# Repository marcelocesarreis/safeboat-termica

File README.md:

# SAFEBOAT Térmica

Sistema de manutenção preditiva por visão térmica com IA para embarcações.
Câmera térmica própria — **MLX90640 (32×24 px) + ESP32-C3 SuperMini** — em case
estanque Ø50×62 mm impresso em ASA, com conexão Wi-Fi e alimentação 12 V do barco.

## Página do projeto

```
node server.cjs        # http://localhost:8097  (launch.json: "safeboat-termica")
```

A página (`public/index.html`) contém: visualizador 3D com vista explodida,
demo **ao vivo** da rede de análise com 3 câmeras mocadas, método de
comparação/detecção, esquema elétrico, cabeamento, fixação, fabricação e BOM.

## Rede de análise (`public/engine.js`)

Implementação de referência do pipeline, idêntica no navegador (mock) e em Node:

1. Aquisição 32×24 @ 4 Hz por I²C, dentro da câmera
2. Normalização (Ta do sensor)
3. Baseline por pixel (média+σ, Welford) por regime de operação
4. Comparação: Δ e z-score (anomalia: z>4 **e** Δ>6 °C)
5. Blobs (componentes conectados ≥3 px)
6. Persistência temporal (≥3 frames)
7. Classificação por zona de equipamento + severidade
8. Alerta com diagnóstico sugerido

Com hardware real: `public/bancada.html` (USB) já alimenta o detector com quadros do sensor.
Rede: ver `firmware/PLANO-WIFI.md` — HTTPS para o hub, receita do VIB, sem MQTT.

## Hardware

- Módulo MLX90640 (GY-MCU90640) via I²C (GPIO8/9, 400 kHz) no ESP32-C3
- Buck MP1584EN 12→5 V + TVS SMBJ26A; MLX no 3V3 do ESP
- Janela frontal de **germânio Ø25×1** (vidro comum bloqueia 8–14 µm);
  alternativa de bancada: filme HDPE 0,25 mm no mesmo recesso
- Vedação (rev. C): tampa de **baioneta 60°** + O-ring NBR 37×3 radial + prensa-cabo M12 IP68
  (a rosca impressa da rev. B falhou: 0,50 mm de engajamento contra 0,20–0,45 mm de erro de FDM)

## CAD paramétrico

```
node tools/generate-stl.cjs    # regenera stl/*.stl (corpo, tampa, carrier, suporte)
```

Mesma receita validada no projeto Vigia (`../safeboat-camera-nv`).

## Retomar o projeto em outra máquina

Este ramo (`projeto`) tem o código-fonte completo; o ramo `main` é só o site publicado no GitHub Pages
(cópia de `public/` + `stl/` + `firmware/`).

```
git clone -b projeto https://github.com/marcelocesarreis/safeboat-termica.git
cd safeboat-termica
npm install            # JSCAD, three, pngjs (CAD e página)
npm start              # servidor local + hub de teste em http://localhost:8097  (Bancada: /bancada.html)
npm run stl            # regenera os STL da rev. C;  node tools/verify-fit.cjs confere a montagem
node tools/test-parser.cjs
```

Firmware (placa ESP32-C3 SuperMini + MLX90640, fonte em `firmware/termica/termica.ino`, versão atual 0.2.8):

```
arduino-cli core install esp32:esp32@3.3.10
arduino-cli lib install "Adafruit MLX90640"
arduino-cli compile --fqbn esp32:esp32:esp32c3:CDCOnBoot=cdc,PartitionScheme=min_spiffs --build-path firmware/build-termica firmware/termica
arduino-cli upload -p COMx --fqbn esp32:esp32:esp32c3:CDCOnBoot=cdc,PartitionScheme=min_spiffs --input-dir firmware/build-termica
```

Use sempre a MESMA `--build-path` (a primeira compilação é longa; as seguintes são rápidas). Os binários prontos da
0.2.8 estão em `firmware/build-termica-0.2.8/` — dá para gravar sem compilar. Ferramentas Python (`pip install pyserial bleak`):
`tools/wifi-cmd.py` (comandos pela USB; recusa o comando de senha), `tools/ble-test.py` (teste do Bluetooth), `tools/serial-dump.py`.

Estado em 19/09/2026: USB, Wi-Fi (HTTPS ao hub, sem MQTT) e Bluetooth LE funcionando; o sensor MLX90640 parou de
responder no I²C (conferir os 4 fios 3V3/GND/GPIO8=SDA/GPIO9=SCL). Próxima etapa: 0.3, detector a bordo — ver `firmware/PLANO-WIFI.md`.
A senha do Wi-Fi fica só na NVS da placa (digitada na Bancada pela USB); não está em nenhum arquivo do repositório.

## Hardware — PCB v1 (22/09/2026)

Placa própria em `hardware/pcb/` (KiCad 10, gerada por script): **quadrada 32 × 32 mm** para o case cúbico do render
(~36 mm externo), **montagem completa na JLCPCB (Standard, dois lados)**: ESP32-C3-MINI-1 + buck AP63203 (12 V → 3,3 V)
+ proteção (PPTC, TVS, SS34) + borne parafuso 12 V + JST p/ rabicho USB na ré; **MLX90640 110°×75°** (TO-39, THT) na
frente. Mesma pinagem do firmware (SDA 8 / SCL 9 / LED 10) + GPIO4 (corta o sensor) e GPIO0 (tensão do barco).
Pacote JLCPCB pronto (gerbers + BOM + CPL), esquemático com ERC 0 e netlist conferida contra a placa —
ver `hardware/pcb/README.md`. A versão redonda Ø41,4 (case escotilha, sensor 55°) ficou em `hardware/pcb/kicad/legado-redonda/`;
o corpo rev. D (ombro z=14) e `stl/espacador-pcb.stl` valem só para ela. Case cúbico em JSCAD: a fazer.

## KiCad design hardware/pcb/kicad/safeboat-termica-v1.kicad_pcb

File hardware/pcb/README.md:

# SAFEBOAT TÉRMICA v2 — PCB (KiCad 10) · pacote JLCPCB (montagem completa)

Rev. 2 (reunião de equipe de 22/10/2026). Placa **40 × 40 mm, 4 camadas (F sinais · In1 plano GND · In2 plano 3V3 ·
B sinais), 1,6 mm**, cantos R2, **recortes laterais na antena**. **Montagem completa na JLCPCB (Standard PCBA, dois
lados)**: SMD + JST no lado da ré (F) e o **sensor MLX90640 110°×75° (TO-39, THT) no lado da frente (B)**. Chega
pronta: só soldar os 2 fios de alimentação nos pads e gravar o firmware.

Versões anteriores: redonda Ø41,4 (case escotilha, sensor 55°) em `kicad/legado-redonda/`; quadrada 32 × 32 de 2 camadas
(v1, 22/09) só no histórico do git.

## O que mudou na rev. 2 (pedidos da reunião)

| Pedido | O que foi feito |
|---|---|
| Nada metálico perto da antena | Indutor, botões, JST e diodos saíram do topo; acima de y = +14,35 só existe o módulo. Faixas laterais do módulo só com 0603/0805 e o SOT-23 do PMOS. |
| Diretrizes de layout da Espressif | Antena rente à borda **com recortes de 3,3 mm nos dois lados** ("cut out the base board on both sides of the antenna"), keep-out de cobre nas 4 camadas sob a antena e recortes, plano de GND sólido sob o módulo (In1), vias de GND, 10 µF + 100 nF no 3V3 junto ao pino, RC no EN, USB longe da antena (canto inferior esquerdo). |
| Trilhas a 90° nos pads | Roteador travado em **ninety_degree**: todas as trilhas são ortogonais, entram reto em todos os pads. |
| Menos voltas / mais planos | **4 camadas**: In1 = GND sólido, In2 = 3V3 sólido; o roteador não roteia nos planos (só fura para eles), então sobram poucas trilhas em F/B. |
| Clearance × limites JLC | Isolamento **0,2 mm** (JLC 4 camadas: ≥ 0,127), trilha 0,25, via 0,6/0,3 (JLC ≥ 0,45/0,2), cobre–borda 0,3, furo–furo ≥ 0,5; regras gravadas no `.kicad_pro`. |
| 4 furos de fixação longe da antena | **M2,5 (Ø2,7)** em (±17,5; +3) e (±17,5; −18): padrão 35 × 21 mm; os de cima ficam 11 mm abaixo do início da antena e 7,6 mm fora do recorte. Raio livre de 2,3 mm para a cabeça. |
| Fusível na entrada | Mantido: **F1 PPTC 0,5 A / 60 V** (SMD1812P050TF/60) + fusível 1 A em linha no cabo. |
| Alimentação 8–32 V | O AP63203 (32 V abs. max.) e o TVS de 26 V **saíram**. Entrou **MP4560** (3,8–55 V, 2 A, abs. max. 60 V), **TVS SMBJ33A** (standoff 33 V, clamp 53 V) e capacitores de entrada **4,7 µF/100 V**. Divisor de leitura da tensão virou 330k/15k (55 V → 2,4 V no ADC). |
| Sem conector de alimentação | Borne removido; **pads P1 (+VIN, quadrado) e P2 (GND)** Ø2,6 / furo 1,3 para soldar o fio direto. |

## O que está aqui

| Pasta / arquivo | Conteúdo |
|---|---|
| `kicad/safeboat-termica-v1.kicad_pcb` + `.kicad_pro` | placa roteada (abre no KiCad 10) — DRC: ver `kicad/drc.json` |
| `kicad/safeboat-termica-v1.kicad_sch` · `safeboat-termica-v1-esquematico.pdf` | **esquemático** (ERC; netlist conferida contra a PCB por `compare_netlist.py`) |
| `kicad/render-*.png` · `layout-*.svg` · `revisao/` | renders 3D (com modelos do sensor e dos pads), vistas 2D, pacote para revisão |
| `jlcpcb/safeboat-termica-v1-gerbers.zip` | gerbers 4 camadas + furação (RS-274X / Excellon) — upload no pedido |
| `jlcpcb/BOM-safeboat-termica-v1.csv` · `CPL-safeboat-termica-v1.csv` | BOM (todas as linhas com código LCSC) e posições (U3 = Bottom) |
| `make_board.py` | fase 1: contorno com recortes, furos, footprints próprios (sensor), **netlist pino a pino**, keep-out, planos, DSN a 90° |
| `finish_board.py` · `fix_drc.py` | fase 2: importa o SES do Freerouting, alarga potência, costura de GND, serigrafia + logo, `.kicad_pro`; pós-DRC |
| `gen_schematic.py` · `compare_netlist.py` | esquemático a partir da mesma netlist · conferência esquemático × PCB |
| `check_overlaps.py` · `export_jlcpcb.py` · `make_gerbers.sh` · `pipeline_final.sh` | courtyards reais, recortes, furos · BOM/CPL · gerbers · pipeline completo |
| `lib/` · `make_3d_models.cjs` · `add_models.py` | símbolo/footprint Espressif; modelos 3D próprios (VRML) do sensor |

## Circuito (resumo — netlist completa em `make_board.py`)

- **Entrada 8–32 V**: P1/P2 (fio soldado; fusível 1 A no cabo) → F1 PPTC 0,5 A/60 V → D1 TVS SMBJ33A → D2 SS34 em série
  (inversão de polaridade) → VIN.
- **Buck U2 MP4560** (não síncrono, 2 A): **FREQ R11 200k → 488 kHz**; FB 0,8 V com **R9 47k / R10 15k → 3,31 V**
  (valores básicos da JLC); COMP **R12 68k + C12 1 nF**; BST C8 100 nF; entrada C5 + C11 4,7 µF/100 V; **L1 10 µH
  SWPA5040S** (2,1 A); roda livre **D4 SS36** (60 V); saída C6/C7 2×22 µF. **EN fica flutuante (= ligado)**: o pino tem
  máximo absoluto de 5 V e não pode ir ao VIN.
- **USB de bancada**: J1 JST-PH 4 vias (1 5V · 2 D− · 3 D+ · 4 GND) → D3 SS14 → VIN. Liga só no USB; com o barco ligado o D3 bloqueia.
- **MCU U1 ESP32-C3-MINI-1-N4**: GPIO8 SDA · GPIO9 SCL (+ BOOT SW1) · GPIO10 LED · GPIO4 SENS_OFF · GPIO0 VSENSE
  (R7 330k / R8 15k + C4) · GPIO18/19 USB · EN com R1 10k + C1 1 µF + SW2 RST · C9 10 µF + C10 100 nF.
- **Sensor U3 MLX90640ESF-BAA** (110°; 1 SDA · 2 VDD · 3 GND · 4 SCL) em VDD_MLX = 3V3 via Q1 SI2301 (ligado por
  padrão; GPIO4 alto desliga); C2 100 nF + C3 10 µF; pull-ups R2/R3 2k2 para VDD_MLX.

## Mecânica

- Lente do sensor em (0; −12) da placa (descentrada: o módulo de 16,6 mm ocupa o topo). Lata Ø9,3 × 5,7 mm na frente;
  decisão de 13/10: **lata exposta** pelo furo do case com anel de vedação em volta, sem janela de germânio.
- Ré: JST 6 mm + plugue, indutor 4 mm, botões 2 mm. Case externo ≈ 44 × 44 × 28 mm com paredes de 2 mm.
- Furos M2,5 em (±17,5; +3) e (±17,5; −18) — postes de Ø5 no case, cabeça ≤ Ø4,6.

## Pedido na JLCPCB

1. **PCB**: upload de `jlcpcb/safeboat-termica-v1-gerbers.zip` — **4 camadas**, 1,6 mm, stack-up padrão JLC04161H, HASL ou
   ENIG, 5 unidades.
2. **PCBA Standard, "Both sides"**: upload de `BOM-safeboat-termica-v1.csv` + `CPL-safeboat-termica-v1.csv`. U3 aparece
   com Layer = Bottom; confirmar no viewer que o sensor está do lado oposto ao módulo.
3. **Códigos LCSC** (todas as linhas): U1 C2934569 · U2 **C40133** (MP4560, US$ 4,45) · U3 **C17380659** (MLX90640 110°,
   ~US$ 28, estoque LCSC 34 un. em 13/10) · Q1 C10487 · D1 **C173526** (SMBJ33A) · D2 C8678 · D3 C2480 · D4 **C360444**
   (SS36A) · L1 **C84608** (SWPA5040S-100) · F1 C462518 · J1 C131334 · SW1/SW2 C72443 · LED1 C157740 · C5/C11
   **C337978** (4,7 µF 100 V) · C6/C7 C45783 · C9 C15850 · C3 C19702 · C1 C15849 · 100 nF C14663 · C12 C1588 ·
   R1 C25804 · R2/R3 C4190 · R4/R6 C21190 · R5 C25803 · R7 C23137 · R8/R10 C22809 · R9 C25819 · R11 C25811 · R12 C23231.
   Os de R9/R11/R12/C12/R7/R8 vieram do guia de básicos da JLC — conferir no carrinho (editar peça desmarca a linha).
4. Depois de chegar: soldar os 2 fios nos pads (+VIN no quadrado), gravar o firmware pelo rabicho USB (BOOT + RST).

## Pendências

- Case cúbico em JSCAD (furo da lata + anel, postes M2,5, prensa-cabo na ré).
- Bancada: consumo em 8/12/24/32 V, ripple no VDD do sensor, aquecimento do MP4560, teste de surto.
- Firmware: GPIO4 e GPIO0; engine com FOV 110°.

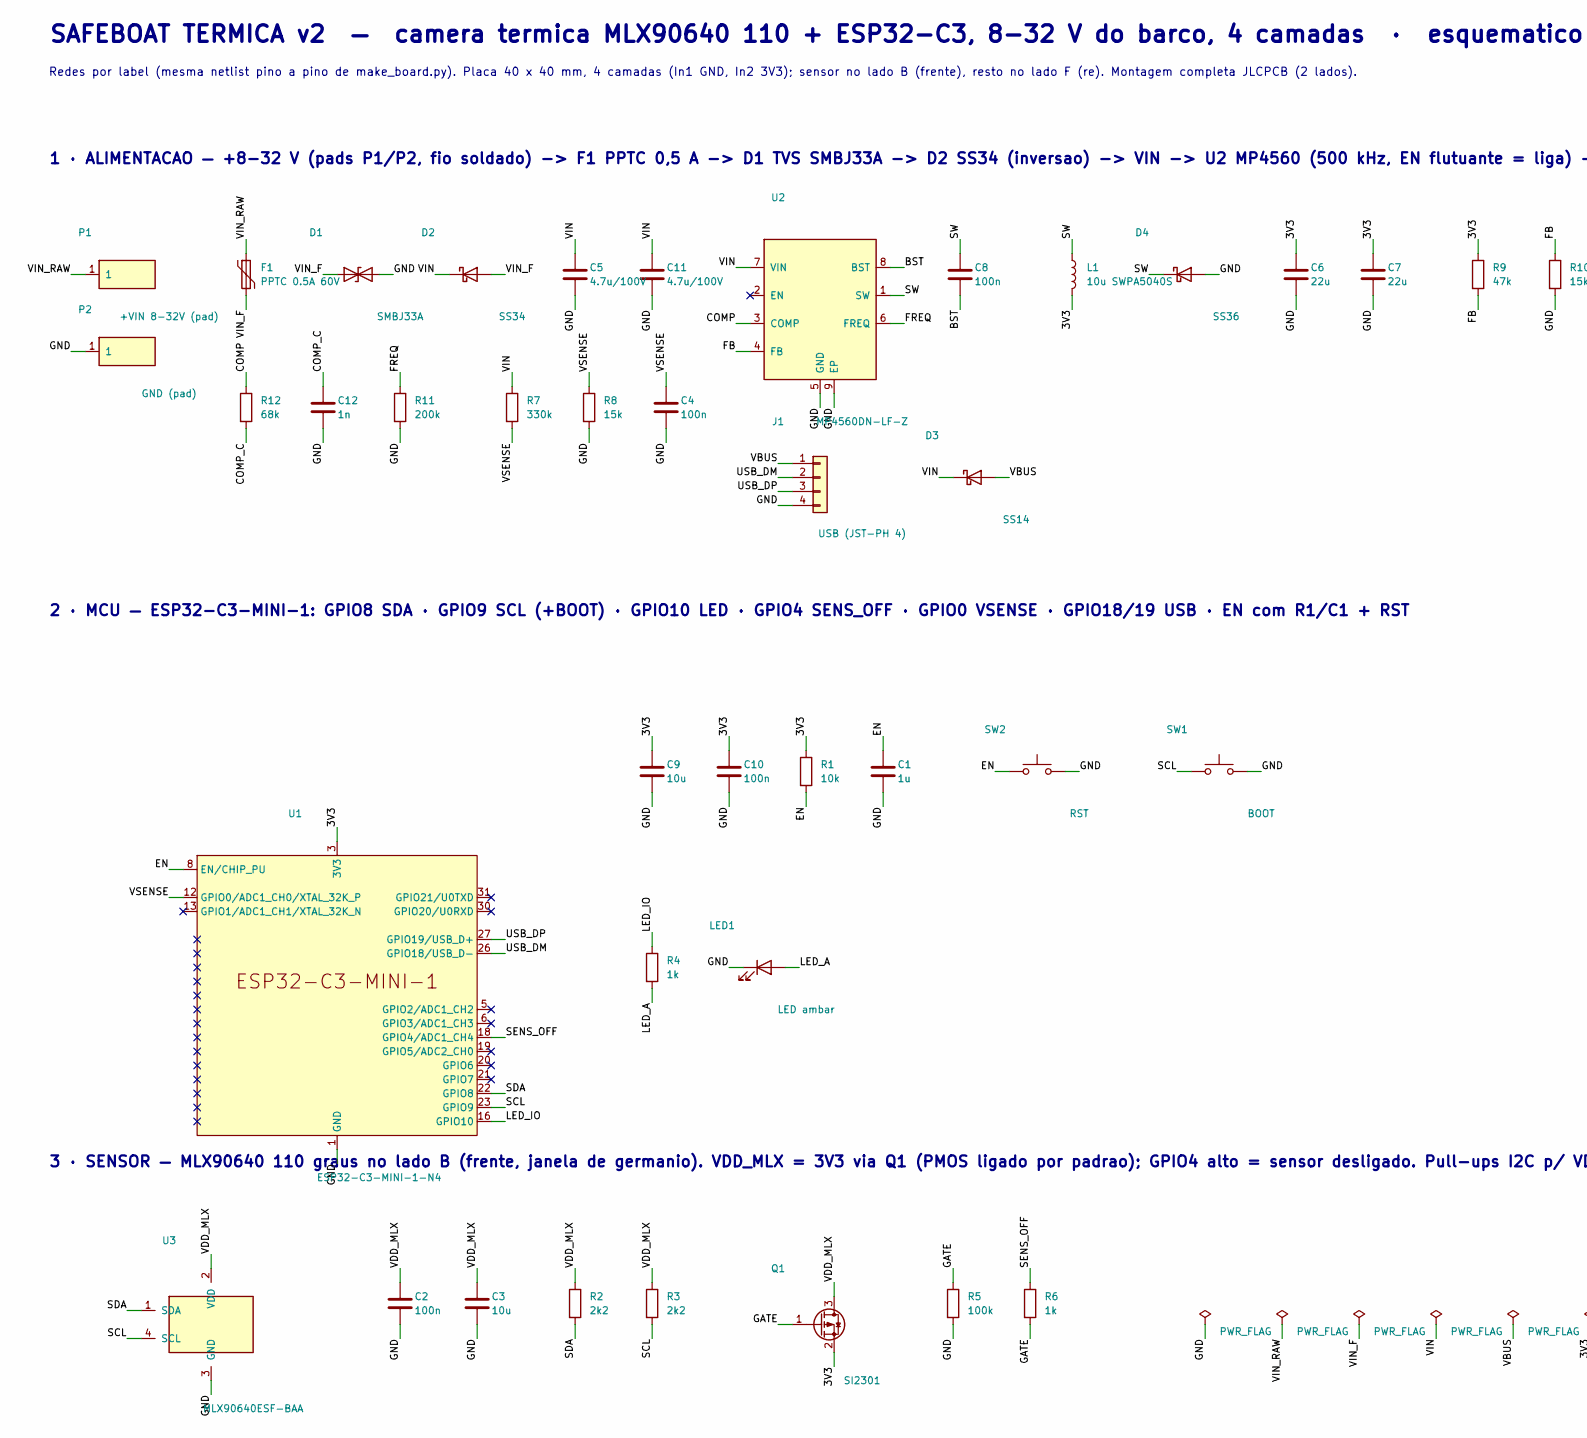
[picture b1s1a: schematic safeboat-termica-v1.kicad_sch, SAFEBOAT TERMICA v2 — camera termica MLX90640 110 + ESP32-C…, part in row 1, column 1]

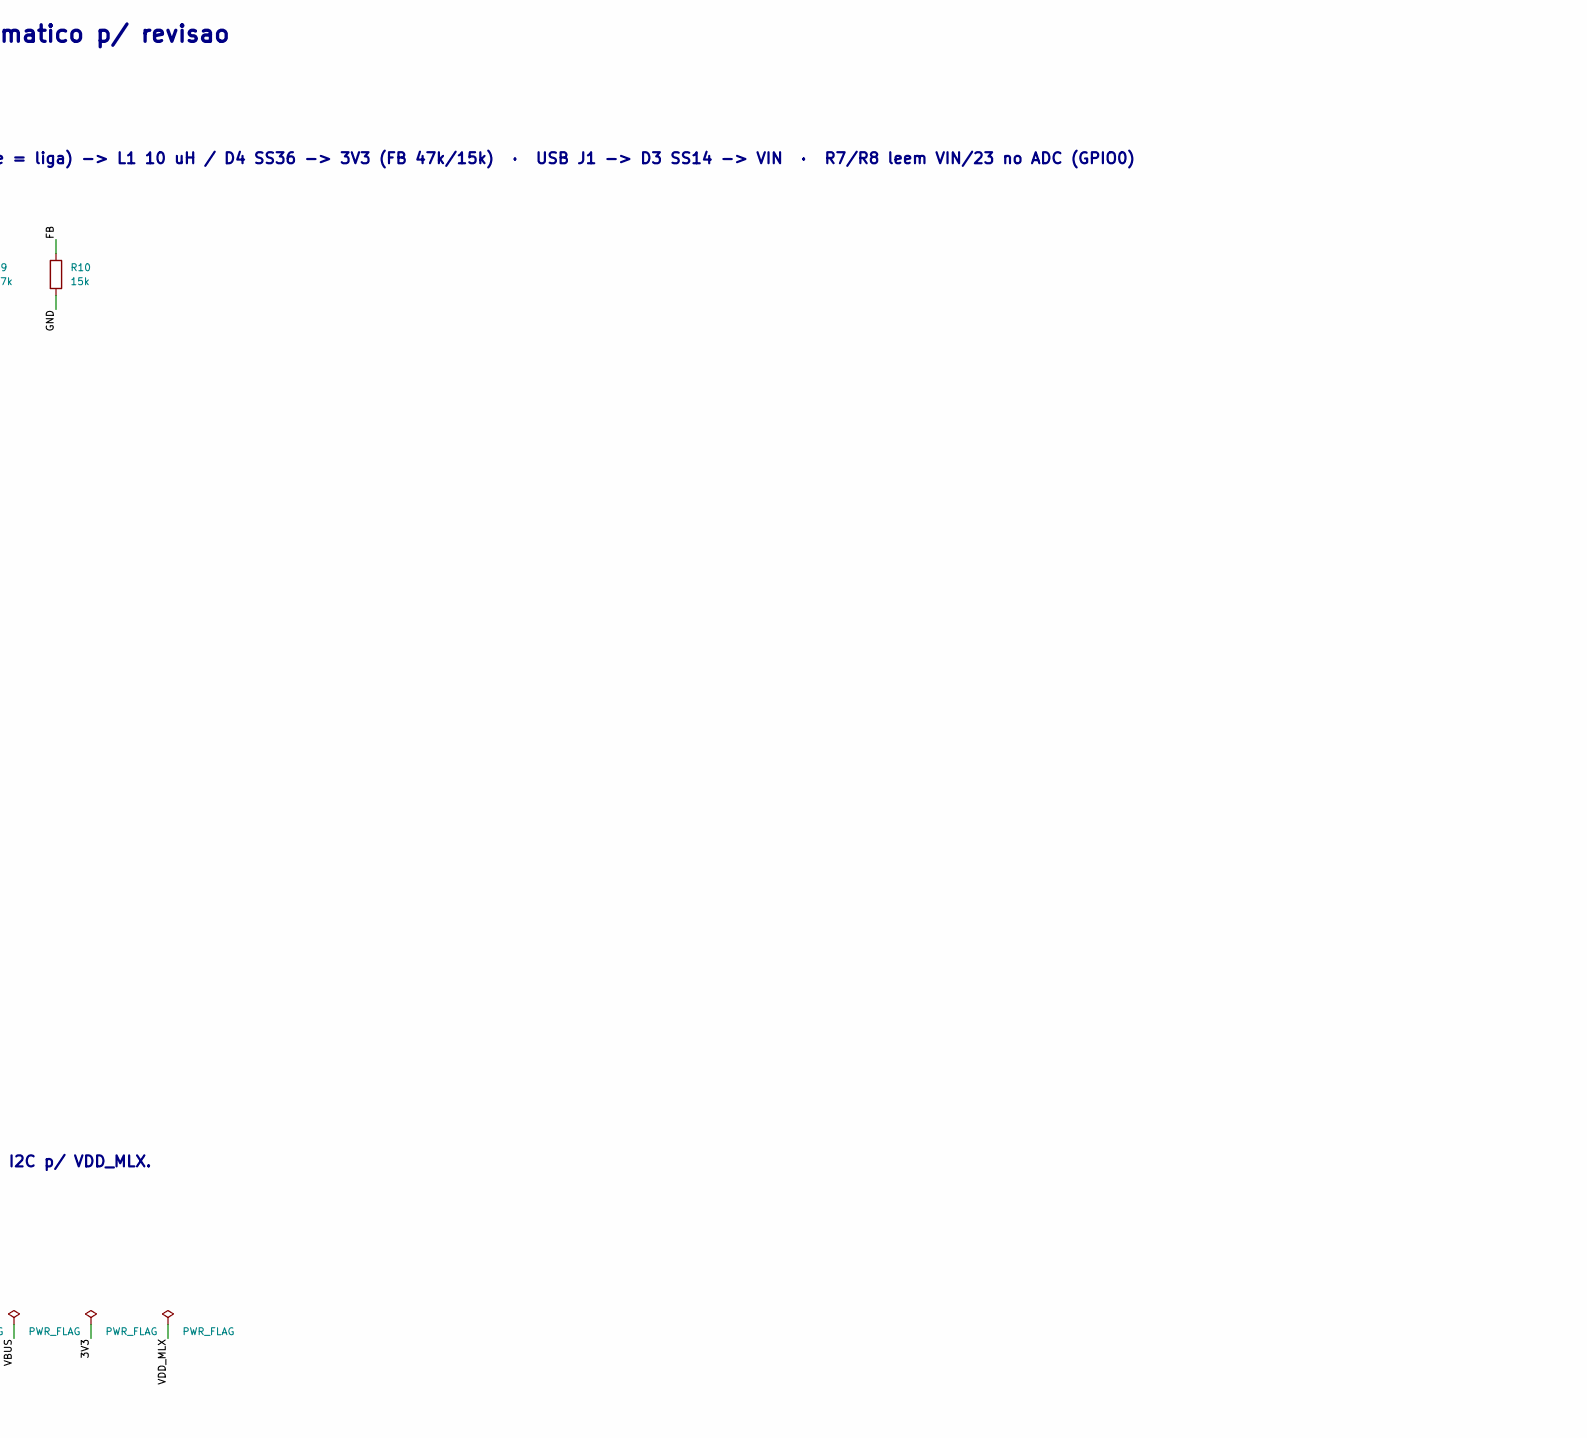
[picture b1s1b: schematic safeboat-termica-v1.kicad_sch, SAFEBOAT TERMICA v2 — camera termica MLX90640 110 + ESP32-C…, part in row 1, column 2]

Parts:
C1: 1u; C_0603_1608Metric
C2, C4, C8, C10: 100n; C_0603_1608Metric
C3: 10u; C_0603_1608Metric
C5, C11: 4.7u/100V; C_1210_3225Metric
C6, C7: 22u; C_0805_2012Metric
C9: 10u; C_0805_2012Metric
C12: 1n; C_0603_1608Metric
D1: SMBJ33A; D_SMB
D2: SS34; D_SMA
D3: SS14; D_SMA
D4: SS36; D_SMA
F1: PPTC 0.5A 60V; Fuse_1812_4532Metric
J1: USB (JST-PH 4); JST_PH_B4B-PH-K_1x04_P2.00mm_Vertical
L1: 10u SWPA5040S; L_Sunlord_SWPA5040S
LED1: LED ambar; LED_0603_1608Metric
P1: +VIN 8-32V (pad); WirePad_P1
P2: GND (pad); WirePad_P2
Q1: SI2301; SOT-23
R1: 10k; R_0603_1608Metric
R2, R3: 2k2; R_0603_1608Metric
R4, R6: 1k; R_0603_1608Metric
R5: 100k; R_0603_1608Metric
R7: 330k; R_0603_1608Metric
R8, R10: 15k; R_0603_1608Metric
R9: 47k; R_0603_1608Metric
R11: 200k; R_0603_1608Metric
R12: 68k; R_0603_1608Metric
SW1: BOOT; SW_Push_1P1T_NO_CK_KMR2
SW2: RST; SW_Push_1P1T_NO_CK_KMR2
U1: ESP32-C3-MINI-1-N4; ESP32-C3-MINI-1
U2: MP4560DN-LF-Z; HSOP-8-1EP_3.9x4.9mm_P1.27mm_EP2.41x3.1mm_ThermalVias
U3: MLX90640ESF-BAA; MLX90640_TO-39

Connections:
3V3: C6.1, C7.1, C9.1, C10.1, L1.2, Q1.2 (S), R1.1, R9.1, U1.3 (3V3)
BST: C8.2, U2.8 (BST)
COMP: R12.1, U2.3 (COMP)
COMP_C: C12.1, R12.2
EN: C1.1, R1.2, SW2.1, U1.8 (EN/CHIP_PU)
FB: R9.2, R10.1, U2.4 (FB)
FREQ: R11.1, U2.6 (FREQ)
GATE: Q1.1 (G), R5.1, R6.2
GND: C1.2, C2.2, C3.2, C4.2, C5.2, C6.2, C7.2, C9.2, C10.2, C11.2, C12.2, D1.2 (A2), D4.2 (A), J1.4, LED1.1 (K), P2.1, R5.2, R8.2, R10.2, R11.2, SW1.2, SW2.2, U1.1 (GND), U1.2 (GND), U1.11 (GND), U1.14 (GND), U1.36 (GND), U1.37 (GND), U1.38 (GND), U1.39 (GND), U1.40 (GND), U1.41 (GND), U1.42 (GND), U1.43 (GND), U1.44 (GND), U1.45 (GND), U1.46 (GND), U1.47 (GND), U1.48 (GND), U1.49 (GND), U1.50 (GND), U1.51 (GND), U1.52 (GND), U1.53 (GND), U2.5 (GND), U2.9 (EP), U3.3 (GND)
LED_A: LED1.2 (A), R4.2
LED_IO: R4.1, U1.16 (GPIO10)
SCL: R3.2, SW1.1, U1.23 (GPIO9), U3.4 (SCL)
SDA: R2.2, U1.22 (GPIO8), U3.1 (SDA)
SENS_OFF: R6.1, U1.18 (GPIO4/ADC1_CH4)
SW: C8.1, D4.1 (K), L1.1, U2.1 (SW)
USB_DM: J1.2, U1.26 (GPIO18/USB_D-)
USB_DP: J1.3, U1.27 (GPIO19/USB_D+)
VBUS: D3.2 (A), J1.1
VDD_MLX: C2.1, C3.1, Q1.3 (D), R2.1, R3.1, U3.2 (VDD)
VIN: C5.1, C11.1, D2.1 (K), D3.1 (K), R7.1, U2.7 (VIN)
VIN_F: D1.1 (A1), D2.2 (A), F1.2
VIN_RAW: F1.1, P1.1
VSENSE: C4.1, R7.2, R8.1, U1.12 (GPIO0/ADC1_CH0/XTAL_32K_P)

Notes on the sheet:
SAFEBOAT TERMICA v2 — camera termica MLX90640 110 + ESP32-C3, 8-32 V do barco, 4 camadas · esquematico p/ revisao
Redes por label (mesma netlist pino a pino de make_board.py). Placa 40 x 40 mm, 4 camadas (In1 GND, In2 3V3); sensor no lado B (frente), resto no lado F (re). Montagem completa JLCPCB (2 lados).
1 · ALIMENTACAO — +8-32 V (pads P1/P2, fio soldado) -> F1 PPTC 0,5 A -> D1 TVS SMBJ33A -> D2 SS34 (inversao) -> VIN -> U2 MP4560 (500 kHz, EN flutuante = liga) -> L1 10 uH / D4 SS36 -> 3V3 (FB 47k/15k) · USB J1 -> D3 SS14 -> VIN · R7/R8 leem VIN/23 no ADC (GPIO0)
2 · MCU — ESP32-C3-MINI-1: GPIO8 SDA · GPIO9 SCL (+BOOT) · GPIO10 LED · GPIO4 SENS_OFF · GPIO0 VSENSE · GPIO18/19 USB · EN com R1/C1 + RST
3 · SENSOR — MLX90640 110 graus no lado B (frente, janela de germanio). VDD_MLX = 3V3 via Q1 (PMOS ligado por padrao); GPIO4 alto = sensor desligado. Pull-ups I2C p/ VDD_MLX.

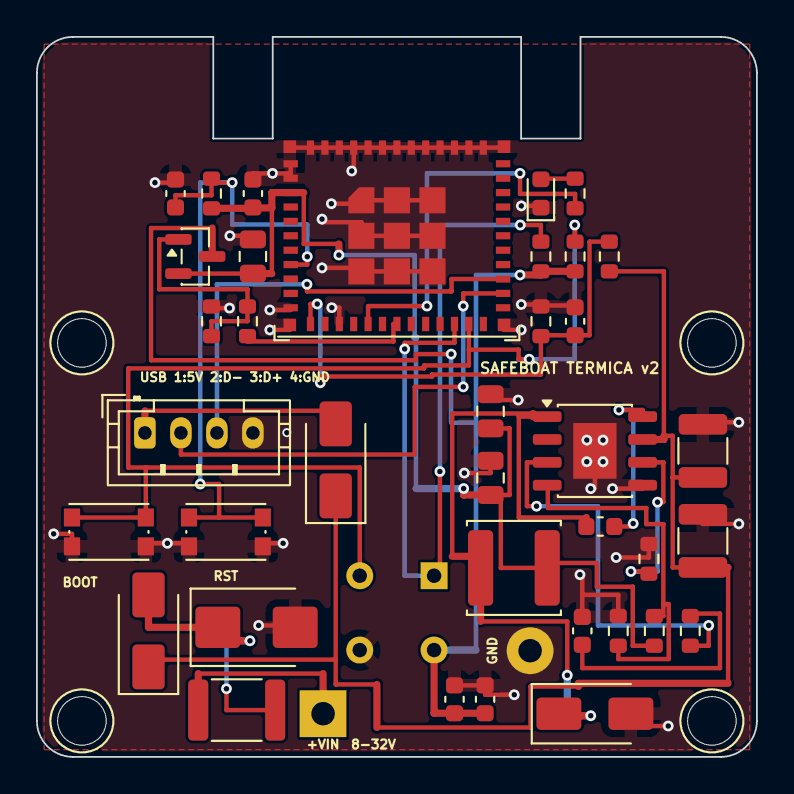
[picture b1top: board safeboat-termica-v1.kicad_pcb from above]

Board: 4 copper layers, 40.0 x 40.0 mm, 44 parts (1 on the bottom side), 23 nets.

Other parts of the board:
H1, H2, H3, H4: M2.5; MountHole_M2.5_NPTH

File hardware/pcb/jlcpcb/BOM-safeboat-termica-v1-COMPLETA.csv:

Comment,Designator,Footprint,LCSC Part #
1uF 0603,C1,C_0603_1608Metric,C15849
100nF 50V X7R 0603,"C10,C2,C4,C8",C_0603_1608Metric,C14663
10uF 0603 X5R,C3,C_0603_1608Metric,C19702
10uF 50V X7R 1210,C5,C_1210_3225Metric,VERIFICAR
22uF 10V X5R 0805,"C6,C7",C_0805_2012Metric,VERIFICAR
10uF 10V X5R 0805,C9,C_0805_2012Metric,basico JLC por valor
SMAJ26A-TR TVS 26V SMA,D1,D_SMA,C132945
SS34 Schottky 3A 40V SMA,D2,D_SMA,VERIFICAR (ex. C8678)
SS14 Schottky 1A 40V SMA,D3,D_SMA,VERIFICAR (ex. C2480)
SMD1812P050TF/60 PPTC 0.5A 60V,F1,Fuse_1812_4532Metric,C462518
JST B4B-PH-K-S 4p 2.0mm,J1,JST_PH_B4B-PH-K_1x04_P2.00mm_Vertical,C131334
KF350-3.5-2P borne 3.5mm 2p,J2,KF350-3.5-2P,C474892
SWPA4020S4R7MT 4.7uH 1.34A,L1,L_Sunlord_SWPA4020S,C48427
LTST-C190KFKT ambar,LED1,LED_0603_1608Metric,C157740
SI2301CDS PMOS SOT-23,Q1,SOT-23,C10487
10k 0603,R1,R_0603_1608Metric,C25804
2.2k 0603,"R2,R3",R_0603_1608Metric,basico JLC por valor
100k 0603,R5,R_0603_1608Metric,C25803
1k 0603,"R4,R6",R_0603_1608Metric,C21190
200k 0603,R7,R_0603_1608Metric,basico JLC por valor
20k 0603,R8,R_0603_1608Metric,basico JLC por valor
KMR221GLFS,"SW1,SW2",SW_Push_1P1T_NO_CK_KMR2,C72443
ESP32-C3-MINI-1-N4,U1,ESP32-C3-MINI-1,C2934569
AP63203WU-7 buck 3.3V 2A 32V,U2,TSOT-23-6,C780769
"MLX90640ESF-BAA-000-TU (TO-39, 110x75 graus) - THT no lado B (frente)",U3,MLX90640_TO-39,C17380659

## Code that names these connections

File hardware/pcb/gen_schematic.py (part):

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text("Redes por label (mesma netlist pino a pino de make_board.py). Placa 40 x 40 mm, 4 camadas (In1 GND, In2 3V3); sensor no lado B (frente), resto no lado F (re). Montagem completa JLCPCB (2 lados).", 20, 24, 1.5)

# ---- 1 · ALIMENTACAO
text("1 · ALIMENTACAO — +8-32 V (pads P1/P2, fio soldado) -> F1 PPTC 0,5 A -> D1 TVS SMBJ33A -> D2 SS34 (inversao) -> VIN -> U2 MP4560 (500 kHz, EN flutuante = liga) -> L1 10 uH / D4 SS36 -> 3V3 (FB 47k/15k)  ·  USB J1 -> D3 SS14 -> VIN  ·  R7/R8 leem VIN/23 no ADC (GPIO0)", 20, 40, 2.0, True)
place("P1", "SAFEBOAT", "WirePad", 34, 60, "+VIN 8-32V (pad)", "SAFEBOAT:WirePad_P1", {"1": "VIN_RAW"}, "fio do cabo soldado direto; fusivel 1 A no cabo")
place("P2", "SAFEBOAT", "WirePad", 34, 74, "GND (pad)", "SAFEBOAT:WirePad_P2", {"1": "GND"}, "retorno")
place("F1", "Device", "Polyfuse", 56, 60, "PPTC 0.5A 60V", "Fuse:Fuse_1812_4532Metric", {"1": "VIN_RAW", "2": "VIN_F"}, "SMD1812P050TF/60 — 2a barreira")
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place("D3", "Device", "D_Schottky", 188, 96, "SS14", FP["SMA"], {"2": "VBUS", "1": "VIN"}, "USB alimenta a placa na bancada (sem 12 V)")

# ---- 2 · MCU
text("2 · MCU — ESP32-C3-MINI-1: GPIO8 SDA · GPIO9 SCL (+BOOT) · GPIO10 LED · GPIO4 SENS_OFF · GPIO0 VSENSE · GPIO18/19 USB · EN com R1/C1 + RST", 20, 122, 2.0, True)
esp = load_symbol("Espressif", "ESP32-C3-MINI-1")
BY_NAME = {"GND": "GND", "3V3": "3V3", "EN": "EN", "GPIO8": "SDA", "GPIO9": "SCL", "GPIO10": "LED_IO", "GPIO4": "SENS_OFF",
           "GPIO0": "VSENSE", "GPIO18": "USB_DM", "GPIO19": "USB_DP"}
esp_nets = {}
nc = []
for p in esp["pins"]:
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R_("R1", 158, 150, "10k", "3V3", "EN", "pull-up EN")
C_("C1", 172, 150, "1u", "EN", "GND", "RC do EN")
place("SW2", "Switch", "SW_Push", 200, 150, "RST", "Button_Switch_SMD:SW_Push_1P1T_NO_CK_KMR2", {"1": "EN", "2": "GND"}, "KMR221GLFS")
place("SW1", "Switch", "SW_Push", 232, 150, "BOOT", "Button_Switch_SMD:SW_Push_1P1T_NO_CK_KMR2", {"1": "SCL", "2": "GND"}, "KMR221GLFS — BOOT = GPIO9 (= SCL; pull-up R3)")
R_("R4", 130, 186, "1k", "LED_IO", "LED_A", "LED de estado (GPIO10)")
place("LED1", "Device", "LED", 150, 186, "LED ambar", "LED_SMD:LED_0603_1608Metric", {"2": "LED_A", "1": "GND"}, "LTST-C190KFKT")

# ---- 3 · SENSOR
text("3 · SENSOR — MLX90640 110 graus no lado B (frente, janela de germanio). VDD_MLX = 3V3 via Q1 (PMOS ligado por padrao); GPIO4 alto = sensor desligado. Pull-ups I2C p/ VDD_MLX.", 20, 222, 2.0, True)
place("U3", "SAFEBOAT", "MLX90640", 50, 250, "MLX90640ESF-BAA", "SAFEBOAT:MLX90640_TO-39", {"1": "SDA", "4": "SCL", "2": "VDD_MLX", "3": "GND"},
      "TO-39 110x75 graus: 1 SDA 2 VDD 3 GND 4 SCL — THT no lado da frente (C17380659)")
C_("C2", 84, 246, "100n", "VDD_MLX", "GND", "desacoplo junto ao VDD (datasheet)")
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R_("R3", 130, 246, "2k2", "VDD_MLX", "SCL", "pull-up I2C (tambem BOOT do ESP)")
place("Q1", "Transistor_FET", "Q_PMOS_GSD", 160, 250, "SI2301", FP["SOT23"], {"1": "GATE", "2": "3V3", "3": "VDD_MLX"}, "PMOS: fonte=3V3, dreno=VDD_MLX")
R_("R5", 184, 246, "100k", "GATE", "GND", "gate a GND = sensor ligado sem firmware")
R_("R6", 198, 246, "1k", "SENS_OFF", "GATE", "GPIO4 -> gate")
for i, net in enumerate(["GND", "VIN_RAW", "VIN_F", "VIN", "VBUS", "3V3", "VDD_MLX"]):
    place("#FLG%d" % (i + 1), "power", "PWR_FLAG", 230 + 14 * i, 250, "PWR_FLAG", "", {"1": net})

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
